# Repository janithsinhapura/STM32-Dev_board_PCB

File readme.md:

#Kicad Project files and PCB manufacturing files of STM32F103C8T6 development board.

PCB Top           | 
:-------------------------:|
  |

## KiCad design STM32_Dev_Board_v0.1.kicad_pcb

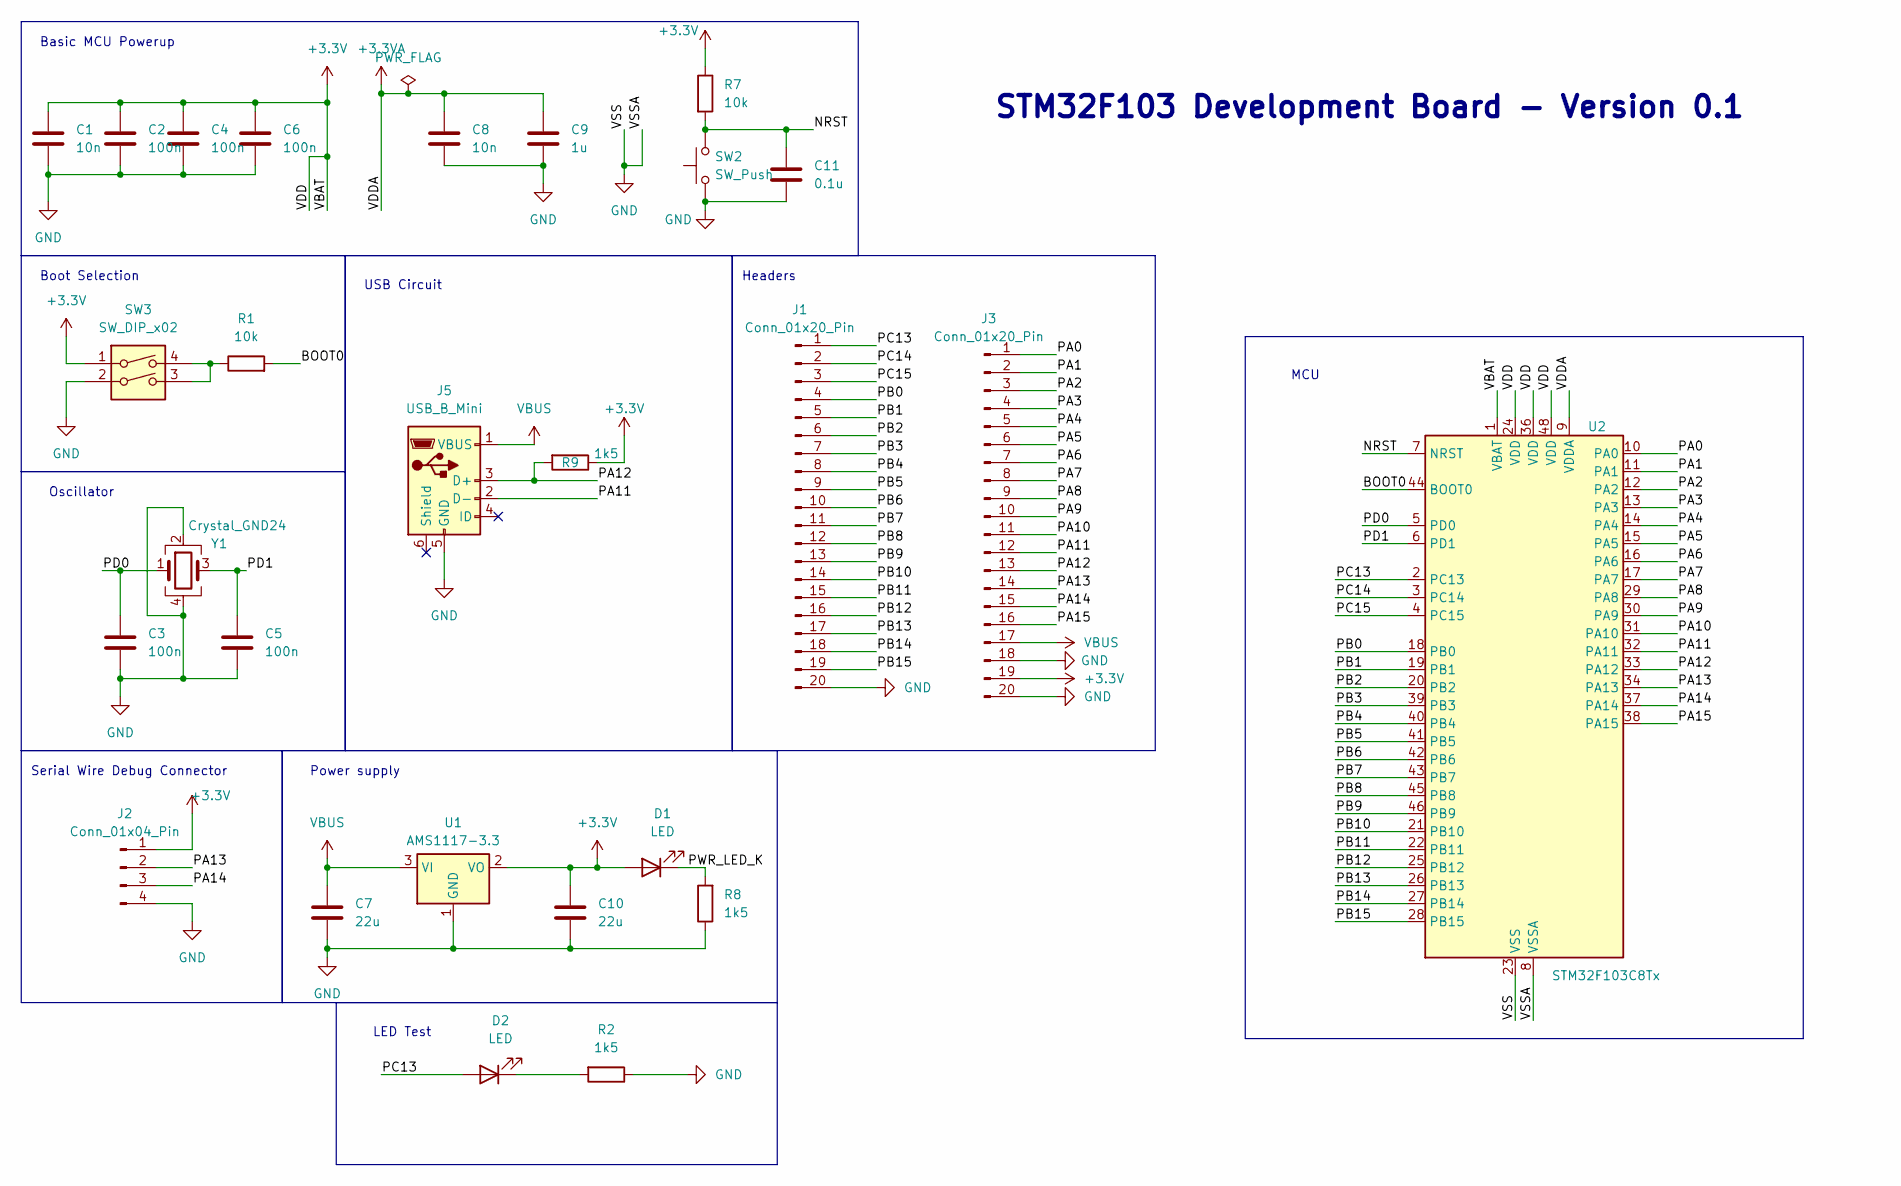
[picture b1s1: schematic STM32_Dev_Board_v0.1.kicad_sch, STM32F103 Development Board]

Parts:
C1, C8: 10n; C_0805_2012Metric_Pad1.18x1.45mm_HandSolder
C2, C3, C4, C5, C6: 100n; C_0805_2012Metric_Pad1.18x1.45mm_HandSolder
C7, C10: 22u; C_0805_2012Metric_Pad1.18x1.45mm_HandSolder
C9: 1u; C_0805_2012Metric_Pad1.18x1.45mm_HandSolder
C11: 0.1u; C_0805_2012Metric_Pad1.18x1.45mm_HandSolder
D1, D2: LED; LED_0805_2012Metric_Pad1.15x1.40mm_HandSolder
J1, J3: Conn_01x20_Pin; PinHeader_1x20_P2.54mm_Vertical
J2: Conn_01x04_Pin; PinHeader_1x04_P2.54mm_Vertical
J5: USB_B_Mini; USB_Micro-B_Wuerth_629105150521
R1, R7: 10k; R_0805_2012Metric_Pad1.20x1.40mm_HandSolder
R2, R8, R9: 1k5; R_0805_2012Metric_Pad1.20x1.40mm_HandSolder
SW2: SW_Push; SW_SPST_CK_RS282G05A3
SW3: SW_DIP_x02; SW_DIP_SPSTx02_Slide_Copal_CHS-02A_W5.08mm_P1.27mm_JPin
U1: AMS1117-3.3; SOT-223-3_TabPin2
U2: STM32F103C8Tx; LQFP-48_7x7mm_P0.5mm
Y1: Crystal_GND24; Crystal_SMD_3225-4Pin_3.2x2.5mm_HandSoldering

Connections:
+3.3V: C1.1, C2.1, C4.1, C6.1, C10.1, D1.2 (A), J2.1, J3.19, R7.1, R9.1, SW3.1, U1.2 (VO), U2.1 (VBAT), U2.24 (VDD), U2.36 (VDD), U2.48 (VDD)
+3.3VA: C8.1, C9.1, U2.9 (VDDA)
/BOOT0: R1.2, U2.44 (BOOT0)
/NRST: C11.1, R7.2, SW2.2, U2.7 (NRST)
/PA0: J3.1, U2.10 (PA0)
/PA1: J3.2, U2.11 (PA1)
/PA2: J3.3, U2.12 (PA2)
/PA3: J3.4, U2.13 (PA3)
/PA4: J3.5, U2.14 (PA4)
/PA5: J3.6, U2.15 (PA5)
/PA6: J3.7, U2.16 (PA6)
/PA7: J3.8, U2.17 (PA7)
/PA8: J3.9, U2.29 (PA8)
/PA9: J3.10, U2.30 (PA9)
/PA10: J3.11, U2.31 (PA10)
/PA11: J3.12, J5.2 (D-), U2.32 (PA11)
/PA12: J3.13, J5.3 (D+), R9.2, U2.33 (PA12)
/PA13: J2.2, J3.14, U2.34 (PA13)
/PA14: J2.3, J3.15, U2.37 (PA14)
/PA15: J3.16, U2.38 (PA15)
/PB0: J1.4, U2.18 (PB0)
/PB1: J1.5, U2.19 (PB1)
/PB2: J1.6, U2.20 (PB2)
/PB3: J1.7, U2.39 (PB3)
/PB4: J1.8, U2.40 (PB4)
/PB5: J1.9, U2.41 (PB5)
/PB6: J1.10, U2.42 (PB6)
/PB7: J1.11, U2.43 (PB7)
/PB8: J1.12, U2.45 (PB8)
/PB9: J1.13, U2.46 (PB9)
/PB10: J1.14, U2.21 (PB10)
/PB11: J1.15, U2.22 (PB11)
/PB12: J1.16, U2.25 (PB12)
/PB13: J1.17, U2.26 (PB13)
/PB14: J1.18, U2.27 (PB14)
/PB15: J1.19, U2.28 (PB15)
/PC13: D2.2 (A), J1.1, U2.2 (PC13)
/PC14: J1.2, U2.3 (PC14)
/PC15: J1.3, U2.4 (PC15)
/PD0: C3.1, U2.5 (PD0), Y1.1
/PD1: C5.1, U2.6 (PD1), Y1.3
/PWR_LED_K: D1.1 (K), R8.2
GND: C1.2, C2.2, C3.2, C4.2, C5.2, C6.2, C7.2, C8.2, C9.2, C10.2, C11.2, J1.20, J2.4, J3.18, J3.20, J5.5 (GND), R2.1, R8.1, SW2.1, SW3.2, U1.1 (GND), U2.8 (VSSA), U2.23 (VSS), U2.35 (VSS), U2.47 (VSS), Y1.2, Y1.4
unnamed: D2.1 (K), R2.2
unnamed: R1.1, SW3.3, SW3.4
VBUS: C7.1, J3.17, J5.1 (VBUS), U1.3 (VI)

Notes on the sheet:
USB Circuit
Basic MCU Powerup
Oscillator
LED Test
MCU
Headers
STM32F103 Development Board - Version 0.1
Serial Wire Debug Connector
Boot Selection
Power supply

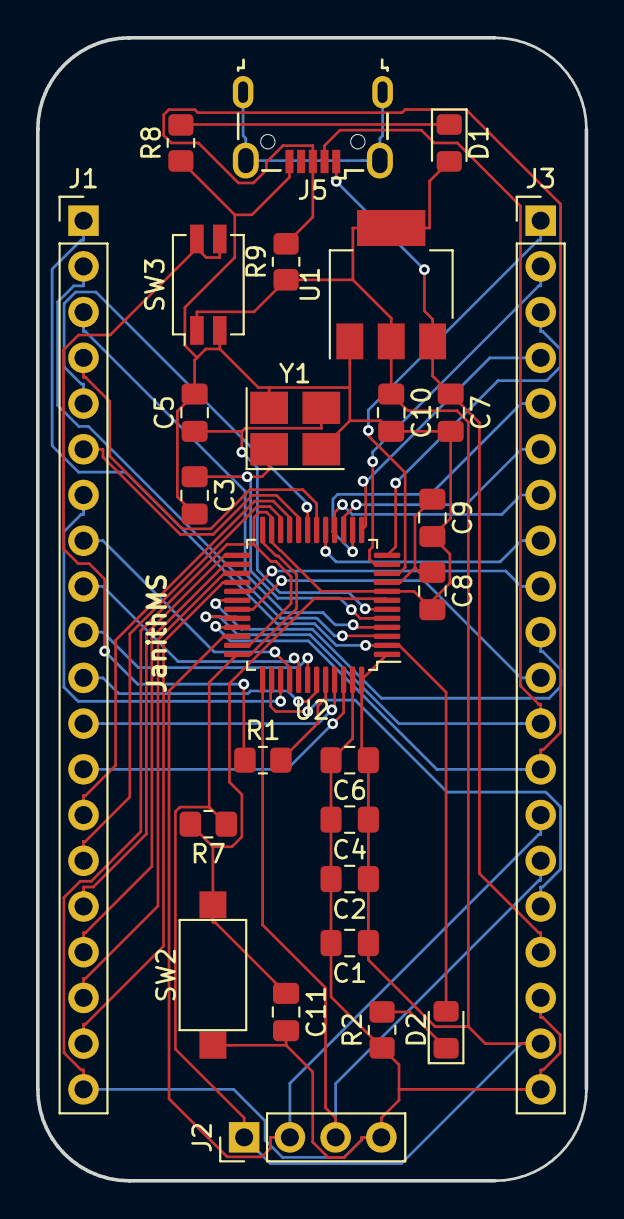
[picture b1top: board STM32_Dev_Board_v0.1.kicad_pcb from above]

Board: 2 copper layers, 30.5 x 63.5 mm, 27 parts (0 on the bottom side), 46 nets.

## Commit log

2023-06-25 Final PCB layout
2023-06-25 add pcb image
